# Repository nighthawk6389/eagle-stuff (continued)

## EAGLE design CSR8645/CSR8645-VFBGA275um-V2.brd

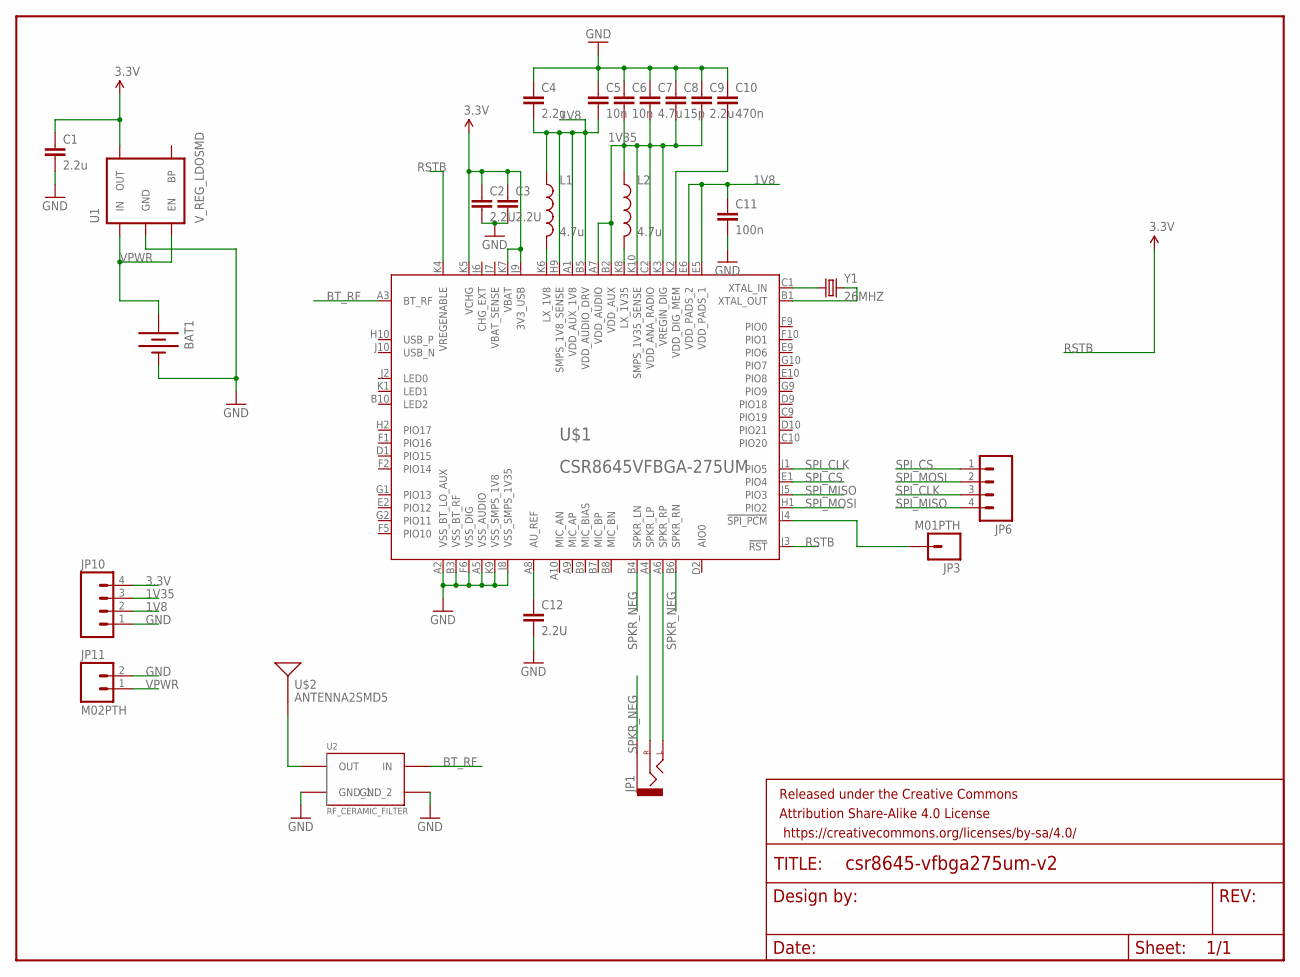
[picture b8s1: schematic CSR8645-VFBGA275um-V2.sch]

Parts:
BAT1: BATTERY9V; BATTCON_9V
C1, C4, C9: 2.2u; 0603-CAP
C2, C3, C12: 2.2U; 0603-CAP
C5, C6: 10n; 0603-CAP
C7: 4.7u; 0603-CAP
C8: 15p; 0603-CAP
C10: 470n; 0603-CAP
C11: 100n; 0603-CAP
FRAME1: FRAME-LETTER; CREATIVE_COMMONS
JP1: AUDIO-JACKSMD2; AUDIO-JACK-3.5MM-SMD
JP3: M01PTH; 1X01
JP6, JP10: M04PTH; 1X04
JP11: M02PTH; 1X02
L1, L2: 4.7u; 0805
U1: V_REG_LDOSMD; SOT23-5
U2: RF_CERAMIC_FILTER; RF_FILTER
U$1: CSR8645VFBGA-275UM; VFBGA68-LARGE
U$2: ANTENNA2SMD5; ANTENNA-CHIP5
Y1: 26MHZ; HC49US

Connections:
1V8: C4.2, C5.2, C11.1, JP10.2, L1.1, U$1.A1 (VDD_AUX_1V8), U$1.B5 (VDD_AUDIO_DRV), U$1.E5 (VDD_PADS_1), U$1.E6 (VDD_PADS_2), U$1.H9 (SMPS_1V8_SENSE)
1V35: C6.2, C7.2, C8.2, C9.2, JP10.3, L2.1, U$1.A7 (VDD_AUDIO), U$1.B2 (VDD_AUX), U$1.C2 (VDD_ANA_RADIO), U$1.K3 (VREGIN_DIG), U$1.K10 (SMPS_1V35_SENSE)
3.3V: C1.1, C2.1, C3.1, JP10.4, U1.5 (OUT), U$1.J9 (3V3_USB), U$1.K5 (VCHG), U$1.K7 (VBAT)
!SPI_PCM: JP3.1, U$1.J4 (!SPI_PCM)
BT_RF: U2.4 (IN), U$1.A3 (BT_RF)
GND: BAT1.-, C1.2, C2.2, C3.2, C4.1, C5.1, C6.1, C7.1, C8.1, C9.1, C10.1, C11.2, C12.2, JP10.1, JP11.2, U1.2 (GND), U2.1 (GND_1), U2.3 (GND_2), U$1.A2 (VSS_BT_LO_AUX), U$1.A5 (VSS_AUDIO), U$1.B3 (VSS_BT_RF), U$1.F6 (VSS_DIG), U$1.J8 (VSS_SMPS_1V35), U$1.K9 (VSS_SMPS_1V8)
unnamed: JP1.RING (RIGHT), U$1.A4 (SPKR_LP)
unnamed: L1.2, U$1.K6 (LX_1V8)
unnamed: L2.2, U$1.K8 (LX_1V35)
unnamed: U$1.C1 (XTAL_IN), Y1.1
unnamed: C10.2, U$1.K2 (VDD_DIG_MEM)
unnamed: U$1.B1 (XTAL_OUT), Y1.2
unnamed: JP1.TIP (LEFT), U$1.A6 (SPKR_RP)
unnamed: U2.2 (OUT), U$2.FEED
unnamed: C12.1, U$1.A8 (AU_REF)
RSTB: U$1.J3 (!RST), U$1.K4 (VREGENABLE)
SPI_CLK: JP6.3, U$1.J1 (PIO5)
SPI_CS: JP6.1, U$1.E1 (PIO4)
SPI_MISO: JP6.4, U$1.J5 (PIO3)
SPI_MOSI: JP6.2, U$1.H1 (PIO2)
SPKR_NEG: JP1.SLEEVE, U$1.B4 (SPKR_LN), U$1.B6 (SPKR_RN)
VPWR: BAT1.+, JP11.1, U1.1 (IN), U1.3 (EN)

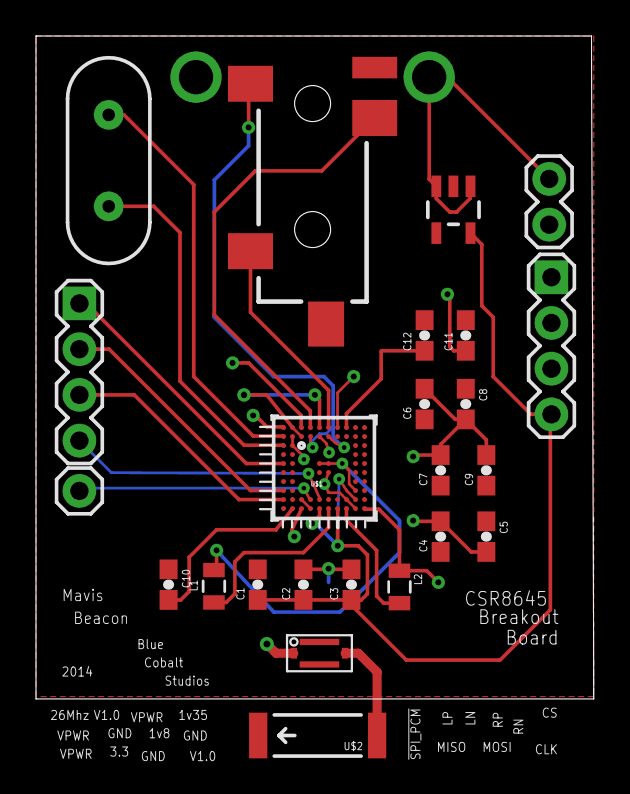
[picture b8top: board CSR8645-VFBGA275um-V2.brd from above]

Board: 4 copper layers, 31.0 x 36.8 mm, 26 parts (1 on the bottom side), 22 nets.

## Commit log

2018-08-03 Initial
